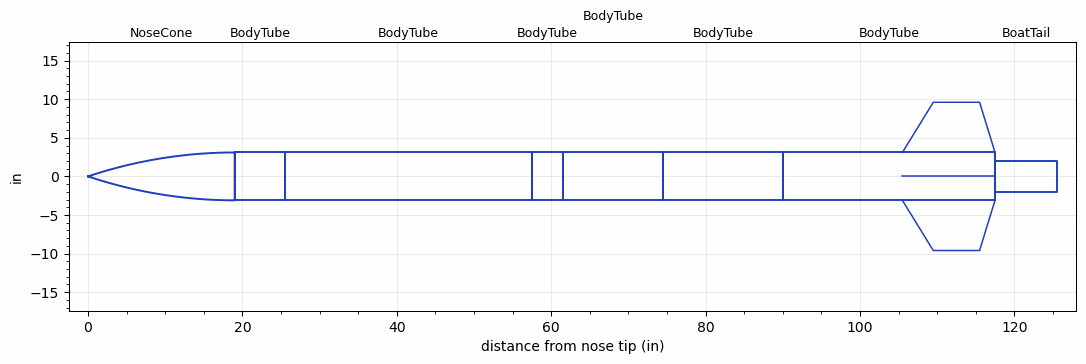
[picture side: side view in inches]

<RASAeroDocument>
 <FileVersion>2</FileVersion>
 <RocketDesign>
  <NoseCone>
   <Length>19</Length>
   <Diameter>6.2</Diameter>
   <Shape>Tangent Ogive</Shape>
   <Location>0</Location>
  </NoseCone>
  <BodyTube>
   <Length>6.5</Length>
   <Diameter>6.2</Diameter>
   <Location>19</Location>
  </BodyTube>
  <BodyTube>
   <Length>31.9999</Length>
   <Diameter>6.2</Diameter>
   <Location>25.4999</Location>
  </BodyTube>
  <BodyTube>
   <Length>4</Length>
   <Diameter>6.2</Diameter>
   <Location>57.4999</Location>
  </BodyTube>
  <BodyTube>
   <Length>13</Length>
   <Diameter>6.2</Diameter>
   <Location>61.4999</Location>
  </BodyTube>
  <BodyTube>
   <Length>15.5</Length>
   <Diameter>6.2</Diameter>
   <Location>74.4999</Location>
  </BodyTube>
  <BodyTube>
   <Length>27.4999</Length>
   <Diameter>6.2</Diameter>
   <RailGuideDiameter>0.621</RailGuideDiameter>
   <RailGuideHeight>0.6845</RailGuideHeight>
   <Location>89.9998</Location>
   <Fin>
    <Count>4</Count>
    <Chord>12</Chord>
    <Span>6.5</Span>
    <SweepDistance>4</SweepDistance>
    <TipChord>6</TipChord>
    <Thickness>0.1875</Thickness>
    <Location>12</Location>
    <AirfoilSection>Rounded</AirfoilSection>
   </Fin>
  </BodyTube>
  <BoatTail>
   <Length>8</Length>
   <Diameter>4</Diameter>
   <RearDiameter>4</RearDiameter>
   <Location>117.4998</Location>
  </BoatTail>
  <Surface>Sheet Metal</Surface>
  <CD>0</CD>
  <ModifiedBarrowman>False</ModifiedBarrowman>
  <Turbulence>False</Turbulence>
  <UseBooster1>False</UseBooster1>
  <UseBooster2>False</UseBooster2>
 </RocketDesign>
 <LaunchSite>
  <Altitude>2870.735</Altitude>
  <Pressure>28.9828</Pressure>
  <RodAngle>5</RodAngle>
  <RodLength>163.9997</RodLength>
  <Temperature>77</Temperature>
  <WindSpeed>15</WindSpeed>
 </LaunchSite>
 <Recovery>
  <Altitude1>1476.378</Altitude1>
  <Altitude2>656.168</Altitude2>
  <DeviceType1>Parachute</DeviceType1>
  <DeviceType2>Parachute</DeviceType2>
  <Event1>True</Event1>
  <Event2>True</Event2>
  <Size1>95.9998</Size1>
  <Size2>22.9</Size2>
  <EventType1>Altitude</EventType1>
  <EventType2>Apogee</EventType2>
  <CD1>2.19</CD1>
  <CD2>0</CD2>
 </Recovery>
 <SimulationList>
  <Simulation>
   <SustainerLaunchWt>66.1378</SustainerLaunchWt>
   <SustainerCG>76.3074</SustainerCG>
   <SustainerIgnitionDelay>0</SustainerIgnitionDelay>
   <Booster1SeparationDelay>0</Booster1SeparationDelay>
   <Booster1IgnitionDelay>0</Booster1IgnitionDelay>
   <IncludeBooster1>False</IncludeBooster1>
   <Booster2Delay>0</Booster2Delay>
   <IncludeBooster2>False</IncludeBooster2>
  </Simulation>
 </SimulationList>
</RASAeroDocument>
